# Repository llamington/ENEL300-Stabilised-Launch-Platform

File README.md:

# ENEL300 Stabilised Launch Platform
Schematic/PCB/Software for a stabilised floating launch platform. Designed for use in the ENEL321 Control Systems course.

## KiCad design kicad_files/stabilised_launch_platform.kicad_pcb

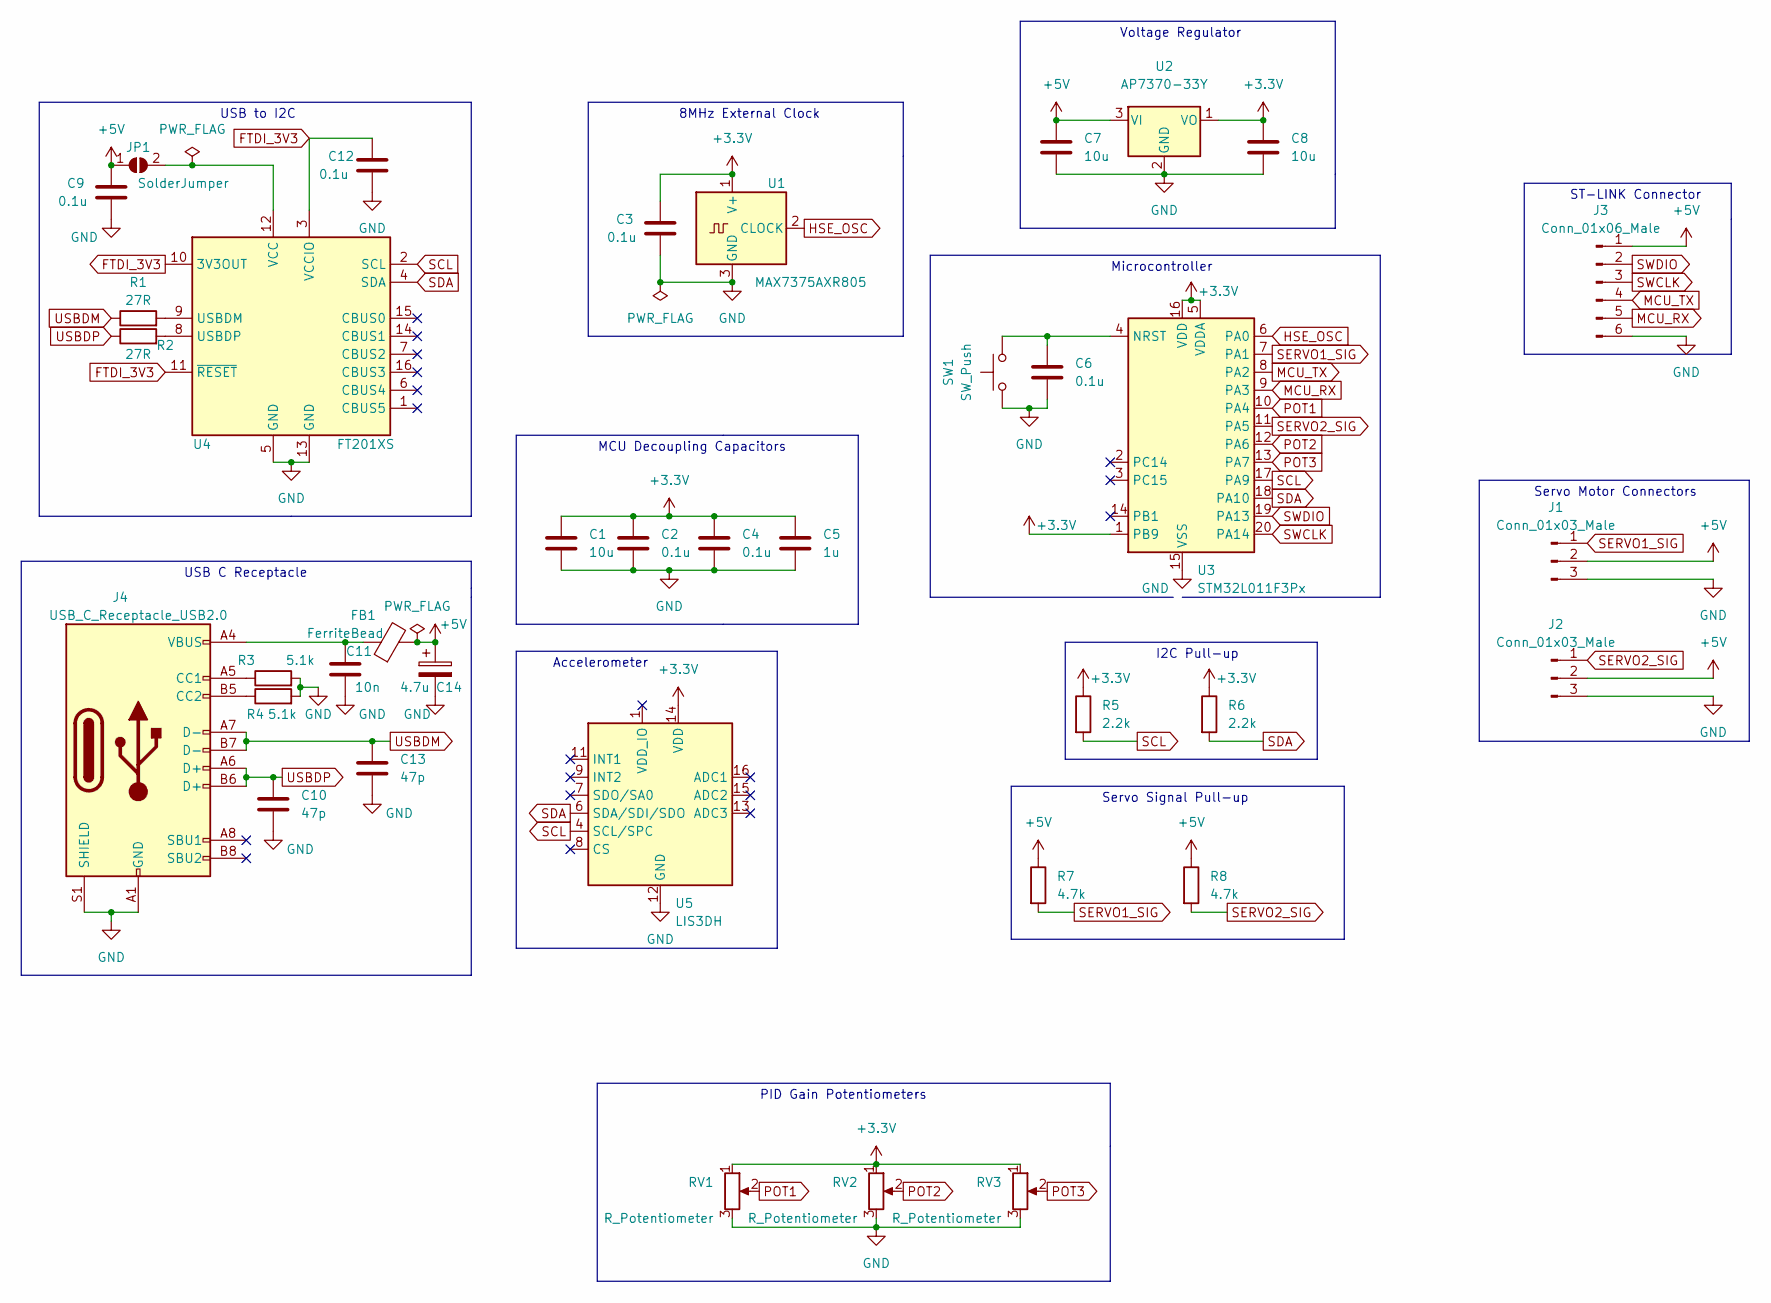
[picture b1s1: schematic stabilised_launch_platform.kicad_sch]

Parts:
C1, C7, C8: 10u; C_0805_2012Metric_Pad1.18x1.45mm_HandSolder
C2, C3, C4, C6, C9, C12: 0.1u; C_0805_2012Metric_Pad1.18x1.45mm_HandSolder
C5: 1u; C_0805_2012Metric_Pad1.18x1.45mm_HandSolder
C10, C13: 47p; C_0805_2012Metric_Pad1.18x1.45mm_HandSolder
C11: 10n; C_0805_2012Metric_Pad1.18x1.45mm_HandSolder
C14: 4.7u; C_0805_2012Metric_Pad1.18x1.45mm_HandSolder
FB1: FerriteBead; L_0805_2012Metric_Pad1.05x1.20mm_HandSolder
J1, J2: Conn_01x03_Male; PinHeader_1x03_P1.00mm_Vertical
J3: Conn_01x06_Male; PinHeader_1x06_P1.00mm_Vertical
J4: USB_C_Receptacle_USB2.0; USB_C_Receptacle_GCT_USB4085
JP1: SolderJumper; SolderJumper-2_P1.3mm_Open_Pad1.0x1.5mm
R1, R2: 27R; R_0805_2012Metric_Pad1.20x1.40mm_HandSolder
R3, R4: 5.1k; R_0805_2012Metric_Pad1.20x1.40mm_HandSolder
R5, R6: 2.2k; R_0805_2012Metric_Pad1.20x1.40mm_HandSolder
R7, R8: 4.7k; R_0805_2012Metric_Pad1.20x1.40mm_HandSolder
RV1, RV2, RV3: R_Potentiometer; Potentiometer_Bourns_PTA4543_Single_Slide
SW1: SW_Push; SW_SPST_PTS645
U1: MAX7375AXR805; SOT-323_SC-70
U2: AP7370-33Y; SOT-89-3
U3: STM32L011F3Px; TSSOP-20_4.4x6.5mm_P0.65mm
U4: FT201XS; SSOP-16_3.9x4.9mm_P0.635mm
U5: LIS3DH; LIS3DH Accelerometer

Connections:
+3.3V: C1.1, C2.1, C3.1, C4.1, C5.1, C8.1, R5.1, R6.1, RV1.1, RV2.1, RV3.1, U1.1 (V+), U2.1 (VO), U3.1 (PB9), U3.5 (VDDA), U3.16 (VDD), U5.14 (VDD)
+5V: C7.1, C9.1, C14.1, FB1.2, J1.2, J2.2, J3.1, JP1.1 (A), R7.1, R8.1, U2.3 (VI)
FTDI_3V3: C12.1, U4.3 (VCCIO), U4.10 (3V3OUT), U4.11 (~RESET)
GND: C1.2, C2.2, C3.2, C4.2, C5.2, C6.2, C7.2, C8.2, C9.2, C10.2, C11.2, C12.2, C13.2, C14.2, J1.3, J2.3, J3.6, J4.A1 (GND), J4.A12 (GND), J4.B1 (GND), J4.B12 (GND), J4.S1 (SHIELD), R3.2, R4.2, RV1.3, RV2.3, RV3.3, SW1.1, U1.3 (GND), U2.2 (GND), U3.15 (VSS), U4.5 (GND), U4.13 (GND), U5.5 (GND), U5.10 (GND), U5.12 (GND); also elsewhere on the board
HSE_OSC: U1.2 (CLOCK), U3.6 (PA0)
MCU_RX: J3.5, U3.9 (PA3)
MCU_TX: J3.4, U3.8 (PA2)
unnamed: C6.1, SW1.2, U3.4 (NRST)
unnamed: C11.1, FB1.1, J4.A4 (VBUS), J4.A9 (VBUS), J4.B4 (VBUS), J4.B9 (VBUS)
unnamed: J4.A5 (CC1), R3.1
unnamed: J4.B5 (CC2), R4.1
unnamed: JP1.2 (B), U4.12 (VCC)
unnamed: R1.2, U4.9 (USBDM)
unnamed: R2.2, U4.8 (USBDP)
POT1: RV1.2, U3.10 (PA4)
POT2: RV2.2, U3.12 (PA6)
POT3: RV3.2, U3.13 (PA7)
SCL: R5.2, U3.17 (PA9), U4.2 (SCL), U5.4 (SCL/SPC)
SDA: R6.2, U3.18 (PA10), U4.4 (SDA), U5.6 (SDA/SDI/SDO)
SERVO1_SIG: J1.1, R7.2, U3.7 (PA1)
SERVO2_SIG: J2.1, R8.2, U3.11 (PA5)
SWCLK: J3.3, U3.20 (PA14)
SWDIO: J3.2, U3.19 (PA13)
USBDM: C13.1, J4.A7 (D-), J4.B7 (D-), R1.1
USBDP: C10.1, J4.A6 (D+), J4.B6 (D+), R2.1

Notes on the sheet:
I2C Pull-up
MCU Decoupling Capacitors
USB to I2C
Servo Signal Pull-up
Voltage Regulator
USB C Receptacle
Servo Motor Connectors
ST-LINK Connector
Accelerometer
8MHz External Clock
PID Gain Potentiometers
Microcontroller

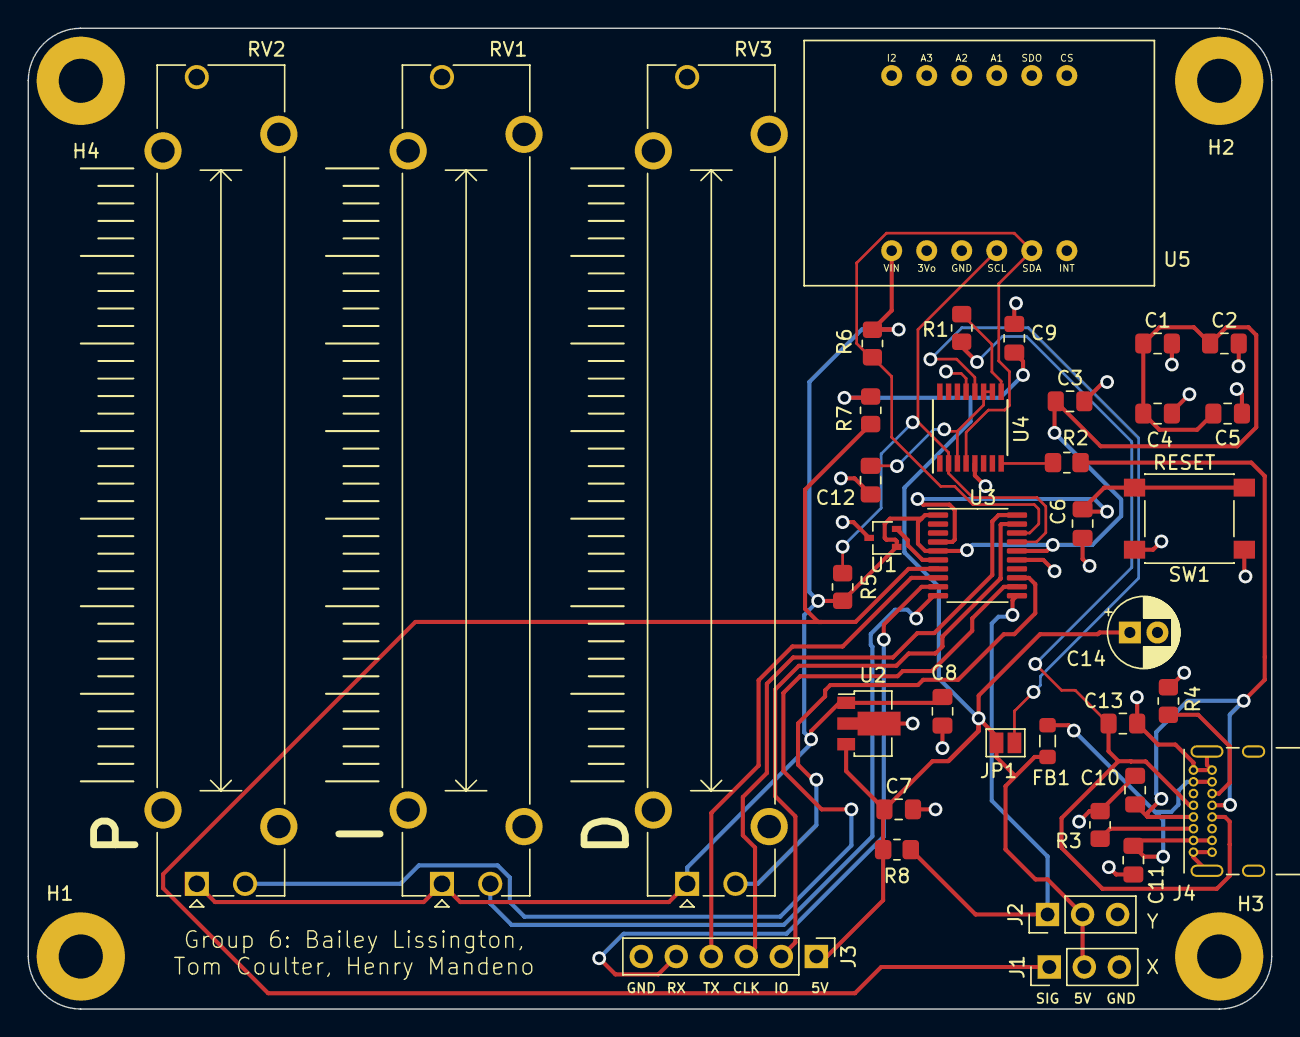
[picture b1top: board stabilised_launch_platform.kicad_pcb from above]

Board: 2 copper layers, 90.2 x 71.1 mm, 41 parts (0 on the bottom side), 25 nets.

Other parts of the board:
H1, H2, H3, H4: MountingHole_Pad; MountingHole_3.2mm_M3_Pad

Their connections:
GND: H1.1, H2.1, H3.1, H4.1; also elsewhere on the board

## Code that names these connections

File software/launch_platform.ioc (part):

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Mcu.Name=STM32L011F(3-4)Px
Mcu.Package=TSSOP20
Mcu.UserName=STM32L011F3Px
PA0-CK_IN.Mode=HSE-External-Clock-Source-for-TinyNemo
PA0-CK_IN.Signal=RCC_CK_IN
PA1.GPIOParameters=GPIO_ModeDefaultPP,GPIO_Label
PA1.GPIO_Label=SERVO1
PA1.GPIO_ModeDefaultPP=GPIO_MODE_AF_OD
PA1.Signal=S_TIM2_CH2
PA10.Mode=I2C
PA10.Signal=I2C1_SDA
PA13.Mode=Serial_Wire
PA13.Signal=SYS_SWDIO
PA14.Mode=Serial_Wire
PA14.Signal=SYS_SWCLK
PA2.Signal=USART2_TX
PA3.Signal=USART2_RX
PA4.GPIOParameters=GPIO_Label
PA4.GPIO_Label=POT1
PA4.Mode=IN4
PA4.Signal=ADC_IN4
PA5.GPIOParameters=GPIO_ModeDefaultPP,GPIO_Label
PA5.GPIO_Label=SERVO2
PA5.GPIO_ModeDefaultPP=GPIO_MODE_AF_OD
PA5.Signal=S_TIM2_CH1
PA6.GPIOParameters=GPIO_Label
PA6.GPIO_Label=POT2
PA6.Mode=IN6
PA6.Signal=ADC_IN6
PA7.GPIOParameters=GPIO_Label
PA7.GPIO_Label=POT3
PA7.Mode=IN7
PA7.Signal=ADC_IN7
PA9.Mode=I2C
PA9.Signal=I2C1_SCL
RCC.HSE_VALUE=8000000
RCC.SYSCLKFreq_VALUE=8000000
RCC.SYSCLKSource=RCC_SYSCLKSOURCE_HSE
board=custom

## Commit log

2022-08-08 created a kicad project
2022-08-08 added kicad template for gitignore
2022-08-15 Added further components to schematic
2022-08-16 component values
2022-08-16 Rough PCB layout, added component footprints
2022-08-18 Added accelerometer and MOSFETs to schematic and PCB
2022-08-18 added more components
2022-08-18 Included custom accelerometer footprint
2022-08-21 kept all baileys code
2022-08-21 Schematic finished
2022-08-21 Removed unnecessary mosfets, schematic finished
2022-08-21 added stm32cube project file
2022-08-22 fixed servo output
2022-08-22 uses makefile for compilation
2022-08-22 PCB tracks routed have all components connected, needs a bit of tidying up
2022-08-22 PCB rearrangments
2022-08-23 PCB modifications: R1 and R2 moved closer to ftdi chip, 3.5mm diameter screw holes added, rounded PCB corners, C14 now electrolyic capacitor
2022-08-23 Screw holes resized
2022-08-23 fixed footprints, added mounting holes, fixed traces
2022-08-23 PCB routing finished
2022-08-23 added labels, passed drc
2022-08-23 moved a couple silkscreen labels
2022-08-26 removed .vscode logs
2022-08-26 removed logfiles from git
2022-08-26 removed uart to save flash storage
2022-08-26 changed .vscode
2022-08-30 separated peripheral blocks
2022-08-31 created an accelerometer module
2022-09-01 created a potentiometers module
2022-09-04 created flag-based data notification for interrupt data
2022-09-04 main loop reads accel/pots
2022-09-04 pid computations
2022-09-04 function to set PID gains
2022-09-05 sets servo duty cycle
2022-09-05 changed mcu to the 16 kB version \
2022-09-12 Changed kicad file names for submission
2022-09-13 elf file now fits in flash
2022-09-14 created an application for testing potentiometers
2022-09-14 acceleration read working
2022-09-15 Working servo motors
2022-09-15 Updated main with changes. Consumes 8100 bytes of flash
2022-09-18 working PID controller
2022-09-18 removed potentiometer module
2022-09-18 merged set gains with compute control
2022-09-18 removed error checking code, created reduced hal
2022-09-18 removed timer error checks
2022-09-20 removed further error checking/filtering code
2022-09-20 Can read accelerometer serially
2022-09-20 updated accelerometer test
2022-09-20 Files for solidworks
2022-09-20 Zip file
2022-09-21 working PI controller
2022-09-21 PID controller appears to be working
2022-09-21 re-added potentiometer code
2022-09-21 working potentiometers
2022-09-21 reading pots better
2022-09-21 PID gains set by potentiometers
